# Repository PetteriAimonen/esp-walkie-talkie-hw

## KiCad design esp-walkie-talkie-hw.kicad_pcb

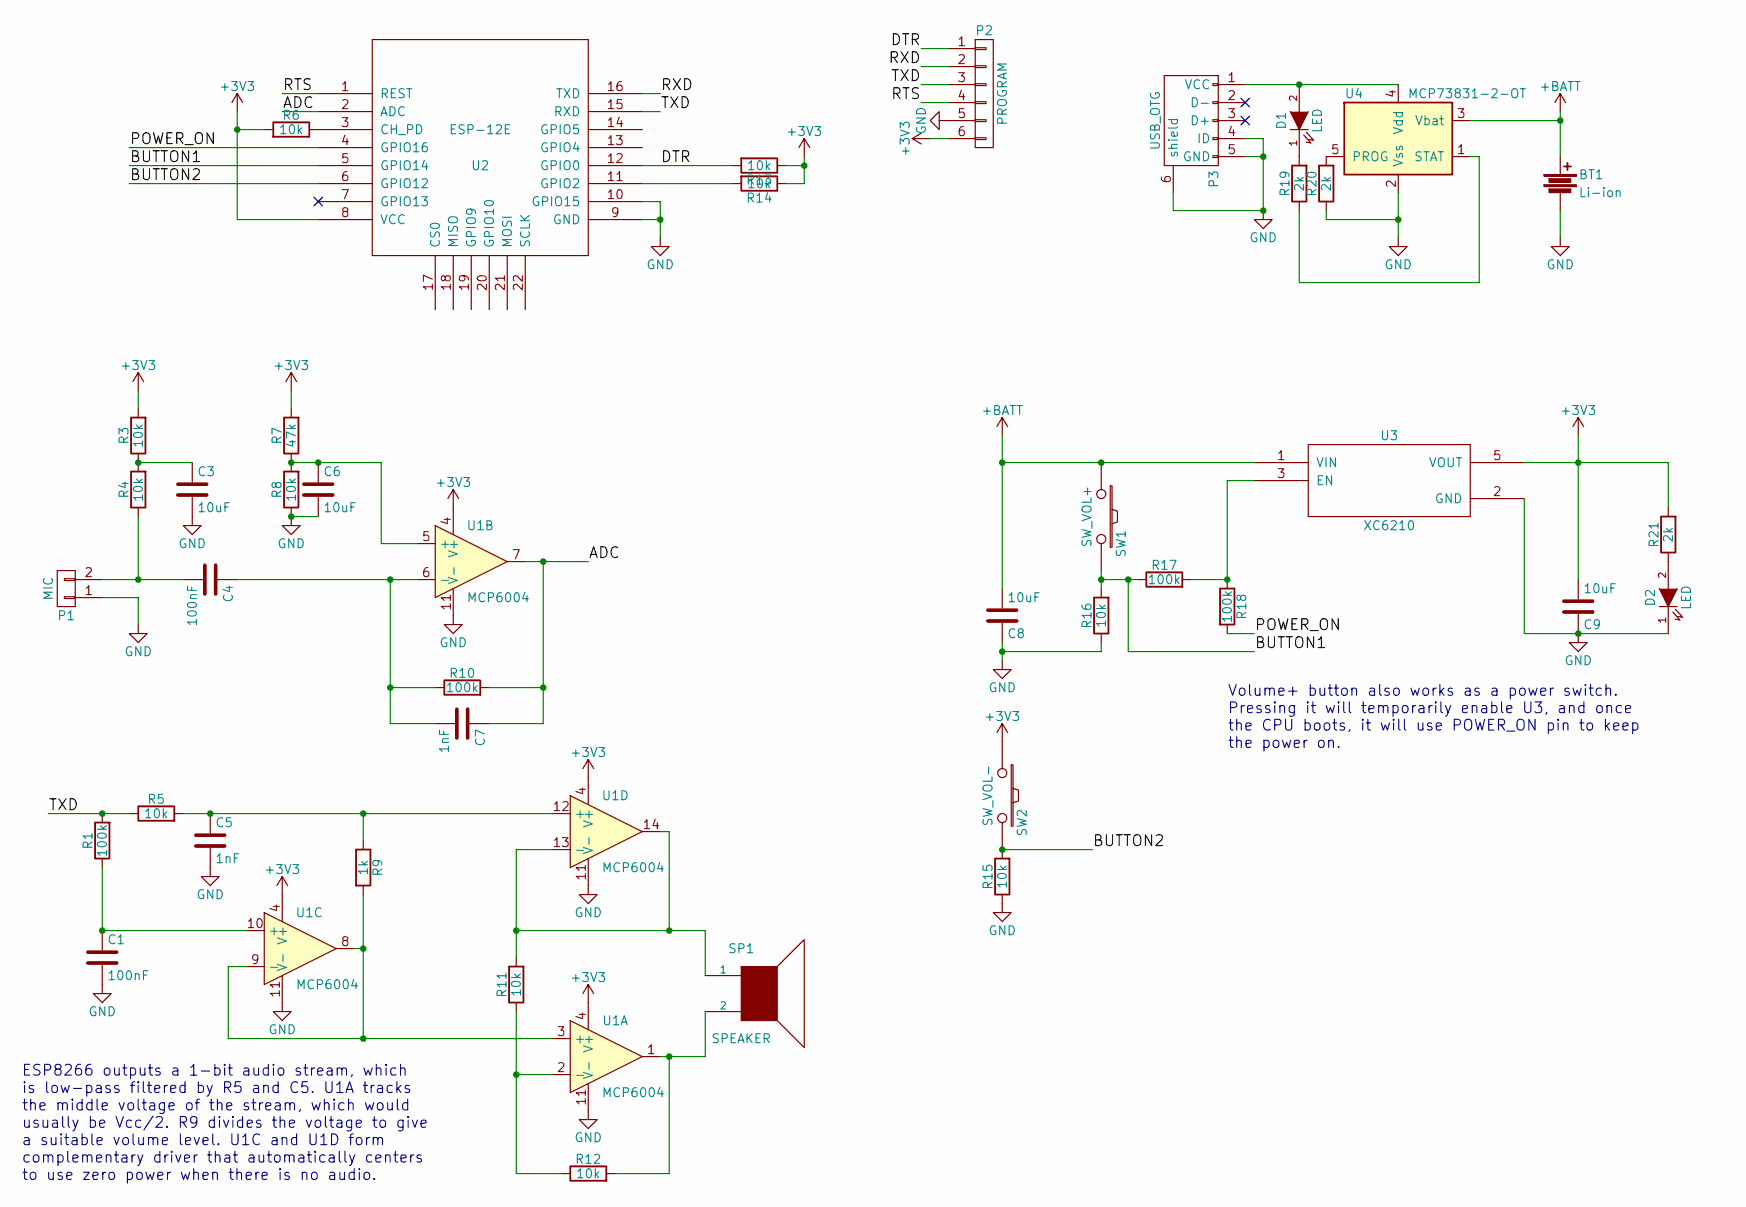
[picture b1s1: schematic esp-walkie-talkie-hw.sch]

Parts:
BT1: Li-ion; Pin_Header_Straight_1x02
C1, C4: 100nF; C_0603
C3, C6, C8, C9: 10uF; C_0805
C5, C7: 1nF; C_0603
D1, D2: LED; LED_0805
P1: MIC; Pin_Header_Straight_1x02
P2: PROGRAM; Pin_Header_Angled_1x06
P3: USB_OTG; USB_Micro-B
R1, R10, R17, R18: 100k; R_0603
R3, R4, R5, R6, R8, R11, R12, R13, R14, R15, R16: 10k; R_0603
R7: 47k; R_0603
R9: 1k; R_0603
R19, R20, R21: 2k; R_0603
SP1: SPEAKER; Pin_Header_Straight_1x02
SW1: SW_VOL+; SW_SPST_EVPBF
SW2: SW_VOL-; SW_SPST_EVPBF
U1: MCP6004; SOIC-14_3.9x8.7mm_Pitch1.27mm
U2: ESP-12E; ESP-12E_SMD
U3: XC6210; SOT-23-5
U4: MCP73831-2-OT; SOT-23-5

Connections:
+3V3: C9.2, P2.6, R3.2, R6.2, R7.2, R13.1, R14.1, R21.2, SW2.1, U1.4 (V+), U2.8 (VCC), U3.5 (VOUT); also elsewhere on the board
+BATT: BT1.1, C8.2, SW1.1, U3.1 (VIN), U4.3 (Vbat)
/ADC: C7.1, R10.2, U1.7, U2.2 (ADC)
/BUTTON1: R16.2, R17.1, SW1.2, U2.5 (GPIO14)
/BUTTON2: R15.2, SW2.2, U2.6 (GPIO12)
/DTR: P2.1, R13.2, U2.12 (GPIO0)
/POWER_ON: R18.2, U2.4 (GPIO16)
/RTS: P2.4, U2.1 (REST)
/RXD: P2.2, U2.16 (TXD)
/TXD: P2.3, R1.2, R5.1, U2.15 (RXD)
GND: BT1.2, C1.2, C3.2, C5.2, C6.2, C8.1, C9.1, D2.1 (K), P1.1, P2.5, P3.4 (ID), P3.5 (GND), P3.6 (shield), R8.1, R15.1, R16.1, R20.1, U1.11 (V-), U2.9 (GND), U2.10 (GPIO15), U3.2 (GND), U4.2 (Vss); also elsewhere on the board
unnamed: C1.1, R1.1, U1.10 (+)
unnamed: C3.1, R3.1, R4.2
unnamed: C4.1, C7.2, R10.1, U1.6 (-)
unnamed: C4.2, P1.2, R4.1
unnamed: C5.1, R5.2, R9.1, U1.12 (+)
unnamed: C6.1, R7.1, R8.2, U1.5 (+)
unnamed: D1.1 (K), R19.2
unnamed: D1.2 (A), P3.1 (VCC), U4.4 (Vdd)
unnamed: D2.2 (A), R21.1
unnamed: R6.1, U2.3 (CH_PD)
unnamed: R9.2, U1.3 (+), U1.8, U1.9 (-)
unnamed: R11.1, R12.1, U1.2 (-)
unnamed: R11.2, SP1.1, U1.13 (-), U1.14
unnamed: R12.2, SP1.2, U1.1
unnamed: R14.2, U2.11 (GPIO2)
unnamed: R17.2, R18.1, U3.3 (EN)
unnamed: R19.1, U4.1 (STAT)
unnamed: R20.2, U4.5 (PROG)

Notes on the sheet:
ESP8266 outputs a 1-bit audio stream, which is low-pass filtered by R5 and C5. U1A tracks the middle voltage of the stream, which would usually be Vcc/2. R9 divides the voltage to give a suitable volume level. U1C and U1D form complementary driver that automatically centers to use zero power when t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
Volume+ button also works as a power switch. Pressing it will temporarily enable U3, and once the CPU boots, it will use POWER_ON pin to keep the power on.

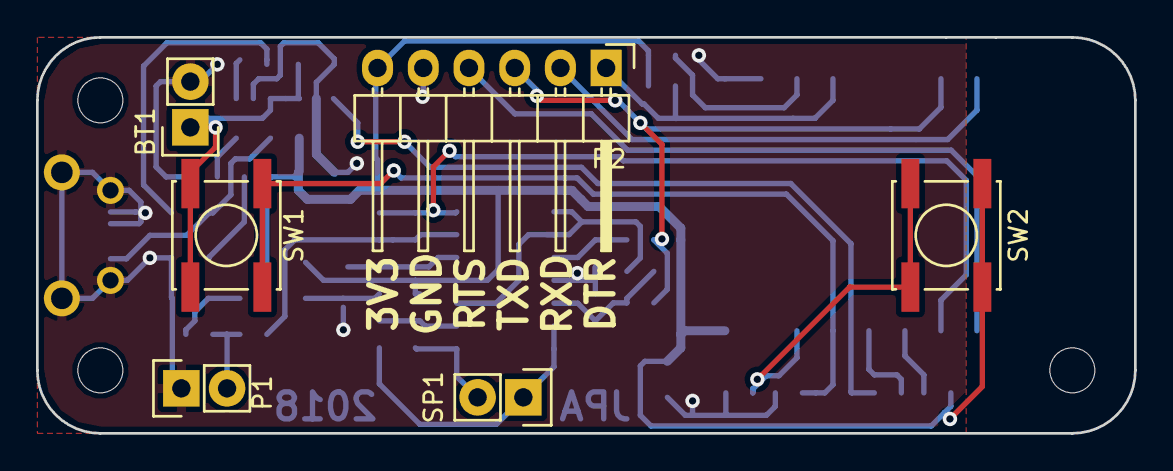
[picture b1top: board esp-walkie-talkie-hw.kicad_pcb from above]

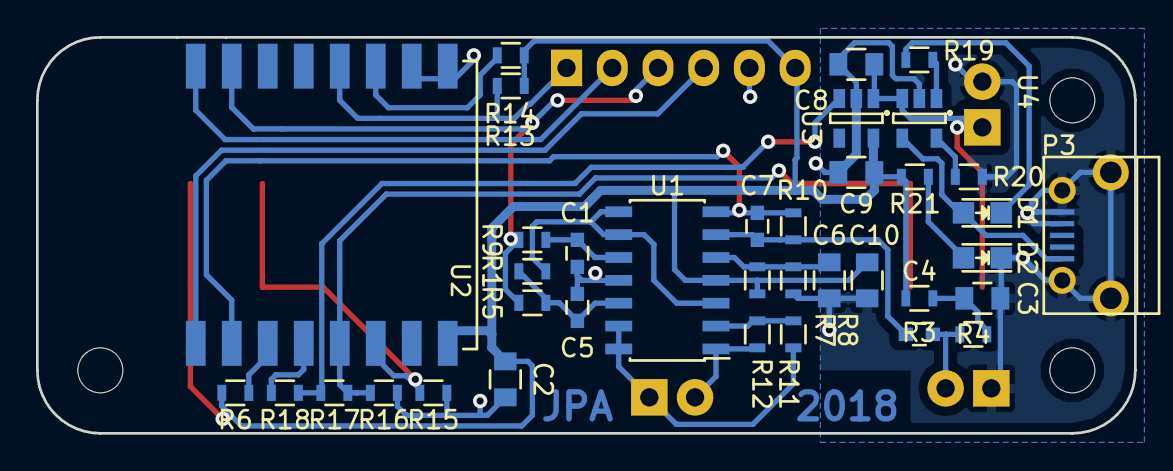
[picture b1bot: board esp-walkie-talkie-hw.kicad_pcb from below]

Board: 2 copper layers, 61.0 x 22.0 mm, 43 parts (37 on the bottom side), 29 nets.

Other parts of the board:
C2, C10: 10uF; C_0805

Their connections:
+3V3: C2.1, C10.1; also elsewhere on the board
GND: C2.2, C10.2; also elsewhere on the board

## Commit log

2018-07-16 First revision pcb
2018-07-16 Add some hacks to try to reduce the noise
